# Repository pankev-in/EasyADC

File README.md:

#EasyADC

##Introduction

This is a brief documentation about EasyADC. But what's is it? 

Just like its name, it is a easy-to-use ADC converter using AVR(basically just plug and play). It is a small device with a ATmega8 on board and can do several things at the same time. If you want to see it in action, please visit my project Website ([k-pan.com](k-pan.com))

This device provides various functions:

1. Read/Test Analog Sensors with- or without a external Terminal. You can either read the value with the on-board LCD 16x2 Display or grab the information from the USB serial port.
2. It comes with an onboard PWM generator too. You can use it as a signal source.

####Specifications:
Connections:
	- 5 x 3.3V 
	- 5 x 5V 
	- 5 x GND 
	- 5 x Analog input port (for ADC)
	- 1 x 5k potentiometer (to adjust PWM signal, but you can also read on lcd or usb)
 	- 1 x PWM output

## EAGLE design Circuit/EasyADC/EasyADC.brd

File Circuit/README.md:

# EasyADC - Circuit

### This board is created with Eagle(V7.3).
### Just import it and should be good to go

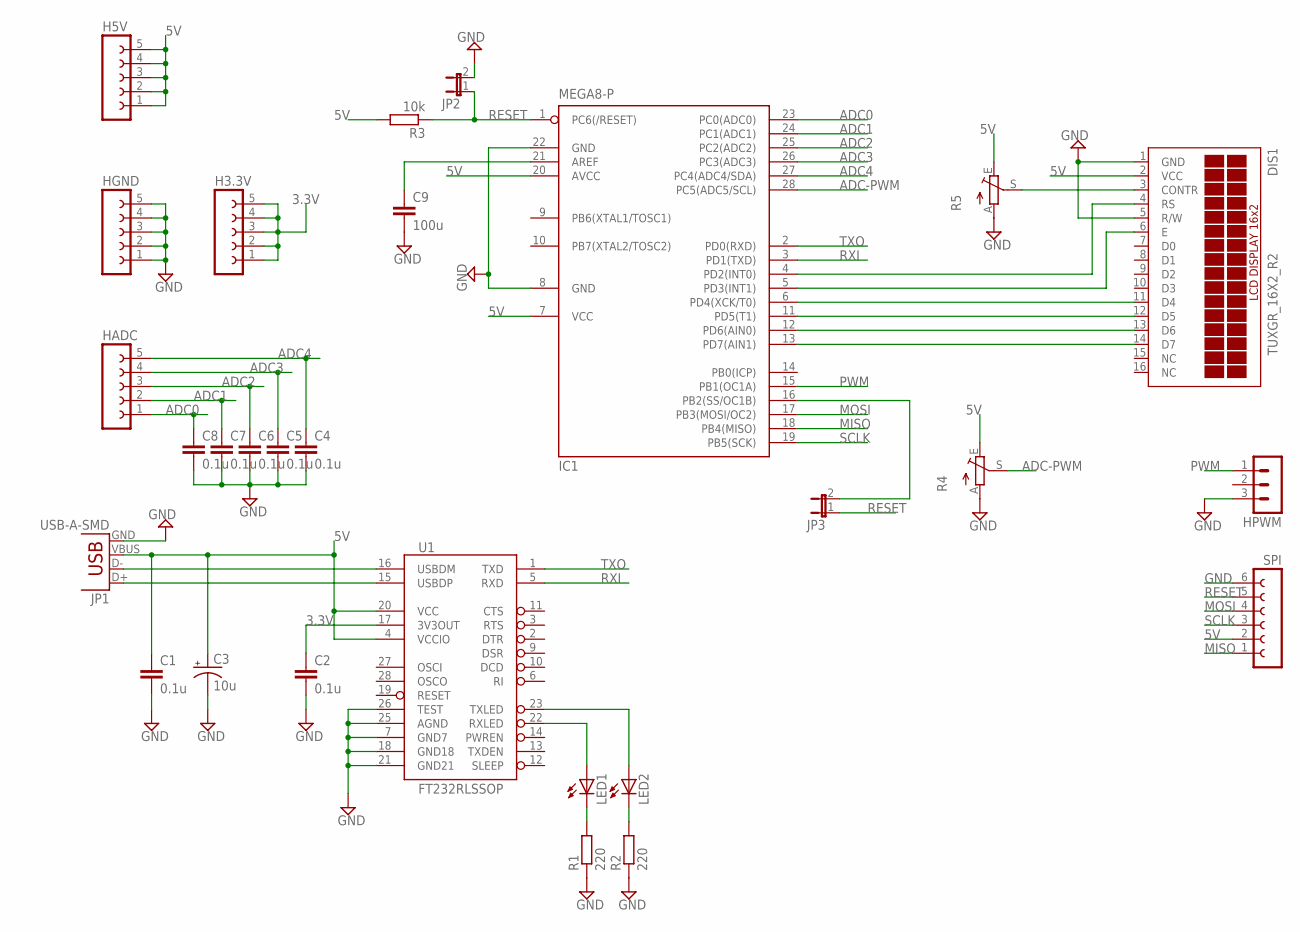
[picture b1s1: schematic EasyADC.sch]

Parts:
C1, C2, C4, C5, C6, C7, C8: 0.1u; C050-045X075
C3: 10u; CPOL-RADIAL-10UF-25V
C9: 100u; C050-075X075
DIS1: TUXGR_16X2_R2
H3.3V, H5V: FE05-1
HADC: FE05-1
HGND: FE05-1
HPWM: MA03-1
IC1: MEGA8-P; DIL28-3
JP1: USB-A-SMD; USB-A-S-NOSILK-FEMALE
JP2, JP3: JUMPER-2PTH; 1X02
LED1, LED2: LED3MM
R1, R2: 220; 0207/10
R3: 10k; 0207/10
R4, R5: TRIM_EU-CA6H; CA6H
SPI: FE06-1; FE06
U1: FT232RLSSOP; SSOP28DB

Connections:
3.3V: C2.1, H3.3V.1, H3.3V.2, H3.3V.3, H3.3V.4, H3.3V.5, U1.17 (3V3OUT)
5V: C1.1, C3.1 (+), DIS1.2 (VCC), H5V.1, H5V.2, H5V.3, H5V.4, H5V.5, IC1.7 (VCC), IC1.20 (AVCC), JP1.VBUS, R3.2, R4.E, R5.E, SPI.2, U1.4 (VCCIO), U1.20 (VCC)
ADC0: C8.1, HADC.1, IC1.23 (PC0(ADC0))
ADC1: C7.1, HADC.2, IC1.24 (PC1(ADC1))
ADC2: C6.1, HADC.3, IC1.25 (PC2(ADC2))
ADC3: C5.1, HADC.4, IC1.26 (PC3(ADC3))
ADC4: C4.1, HADC.5, IC1.27 (PC4(ADC4/SDA))
ADC-PWM: IC1.28 (PC5(ADC5/SCL)), R4.S
GND: C1.2, C2.2, C3.2 (-), C4.2, C5.2, C6.2, C7.2, C8.2, C9.2, DIS1.1 (GND), DIS1.5 (R/W), HGND.1, HGND.2, HGND.3, HGND.4, HGND.5, HPWM.3, IC1.8 (GND), IC1.22 (GND), JP1.GND, JP2.2, R1.1, R2.1, R4.A, R5.A, SPI.6, U1.7 (GND7), U1.18 (GND18), U1.21 (GND21), U1.25 (AGND), U1.26 (TEST)
MISO: IC1.18 (PB4(MISO)), SPI.1
MOSI: IC1.17 (PB3(MOSI/OC2)), SPI.4
unnamed: LED1.A, U1.22 (RXLED)
unnamed: JP1.D-, U1.16 (USBDM)
unnamed: JP1.D+, U1.15 (USBDP)
unnamed: LED2.A, U1.23 (TXLED)
unnamed: LED1.K (C), R1.2
unnamed: LED2.K (C), R2.2
unnamed: DIS1.14 (D7), IC1.13 (PD7(AIN1))
unnamed: DIS1.13 (D6), IC1.12 (PD6(AIN0))
unnamed: DIS1.12 (D5), IC1.11 (PD5(T1))
unnamed: DIS1.11 (D4), IC1.6 (PD4(XCK/T0))
unnamed: DIS1.4 (RS), IC1.4 (PD2(INT0))
unnamed: DIS1.6 (E), IC1.5 (PD3(INT1))
unnamed: DIS1.3 (CONTR), R5.S
unnamed: C9.1, IC1.21 (AREF)
unnamed: IC1.16 (PB2(SS/OC1B)), JP3.2
PWM: HPWM.1, IC1.15 (PB1(OC1A))
RESET: IC1.1 (PC6(/RESET)), JP2.1, JP3.1, R3.1, SPI.5
RXI: IC1.3 (PD1(TXD)), U1.5 (RXD)
SCLK: IC1.19 (PB5(SCK)), SPI.3
TXO: IC1.2 (PD0(RXD)), U1.1 (TXD)

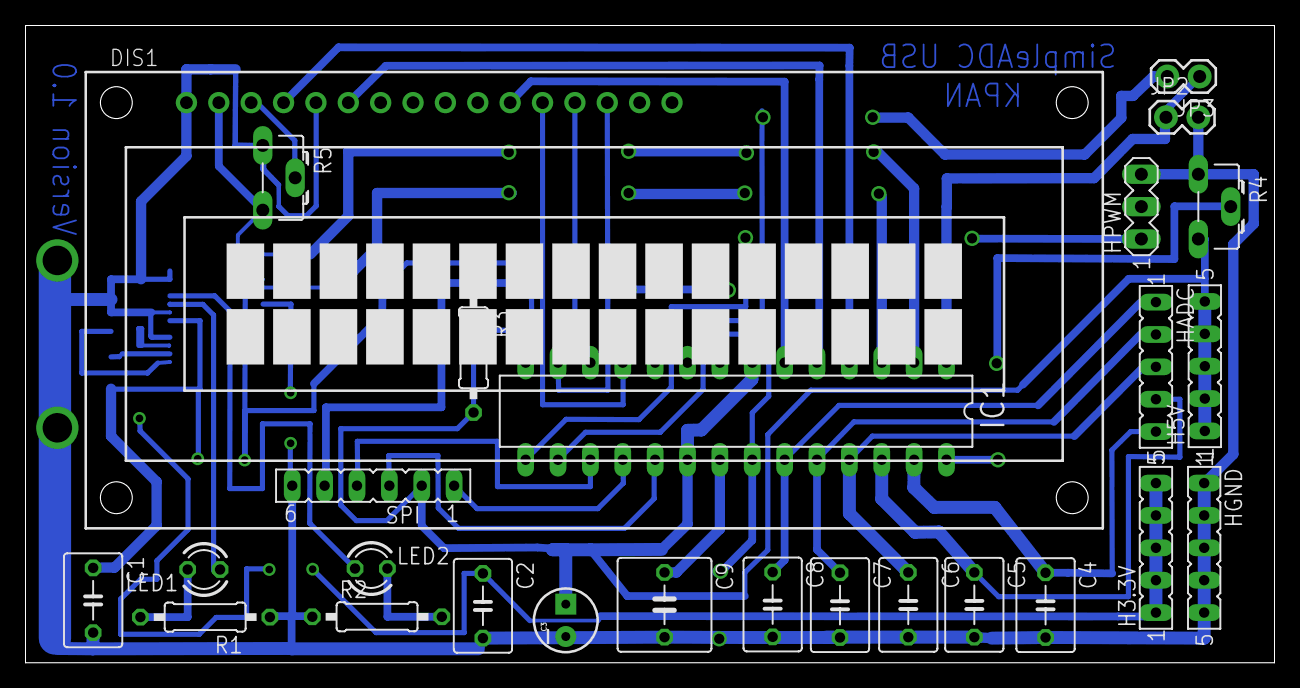
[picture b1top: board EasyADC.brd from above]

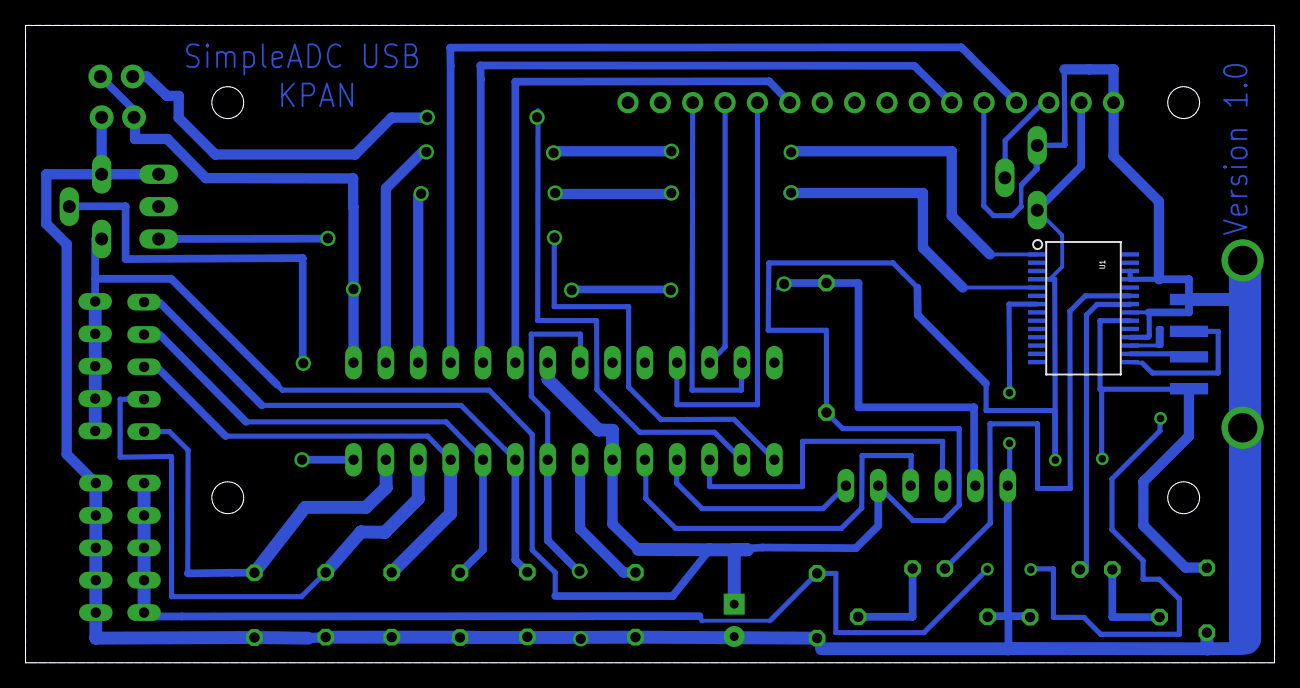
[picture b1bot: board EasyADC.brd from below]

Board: 2 copper layers, 98.0 x 50.0 mm, 28 parts (2 on the bottom side), 31 nets.

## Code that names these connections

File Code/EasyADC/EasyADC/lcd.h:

#ifndef LCD_H
#define LCD_H

////////////////////////////////////////////////////////////////////////////////
// Hier die verwendete Taktfrequenz in Hz eintragen, wichtig!

#ifndef F_CPU
#define F_CPU 8000000
#endif

////////////////////////////////////////////////////////////////////////////////
// Pinbelegung für das LCD, an verwendete Pins anpassen
// Alle LCD Pins müssen an einem Port angeschlossen sein und die 4
// Datenleitungen müssen auf aufeinanderfolgenden Pins liegen

//  LCD DB4-DB7 <-->  PORTD Bit PD4-PD7
#define LCD_PORT      PORTD
#define LCD_DDR       DDRD
#define LCD_DB        PD4

//  LCD RS      <-->  PORTD Bit PD2     (RS: 1=Data, 0=Command)
#define LCD_RS        PD2

//  LCD EN      <-->  PORTD Bit PD3     (EN: 1-Impuls für Daten)
#define LCD_EN        PD3

////////////////////////////////////////////////////////////////////////////////
// LCD Ausführungszeiten (MS=Millisekunden, US=Mikrosekunden)

#define LCD_BOOTUP_MS           15
#define LCD_ENABLE_US           20
#define LCD_WRITEDATA_US        46
#define LCD_COMMAND_US          42

#define LCD_SOFT_RESET_MS1      5
#define LCD_SOFT_RESET_MS2      1
#define LCD_SOFT_RESET_MS3      1
#define LCD_SET_4BITMODE_MS     5

#define LCD_CLEAR_DISPLAY_MS    2
#define LCD_CURSOR_HOME_MS      2

////////////////////////////////////////////////////////////////////////////////
// Zeilendefinitionen des verwendeten LCD
// Die Einträge hier sollten für ein LCD mit einer Zeilenlänge von 16 Zeichen passen
// Bei anderen Zeilenlängen müssen diese Einträge angepasst werden

#define LCD_DDADR_LINE1         0x00
#define LCD_DDADR_LINE2         0x40
#define LCD_DDADR_LINE3         0x10
#define LCD_DDADR_LINE4         0x50

////////////////////////////////////////////////////////////////////////////////
// Initialisierung: muss ganz am Anfang des Programms aufgerufen werden.
void lcd_init( void );

////////////////////////////////////////////////////////////////////////////////
// LCD löschen
void lcd_clear( void );

////////////////////////////////////////////////////////////////////////////////
// Cursor in die 1. Zeile, 0-te Spalte
void lcd_home( void );

////////////////////////////////////////////////////////////////////////////////
// Cursor an eine beliebige Position
void lcd_setcursor( uint8_t spalte, uint8_t zeile );

////////////////////////////////////////////////////////////////////////////////
// Ausgabe eines einzelnen Zeichens an der aktuellen Cursorposition
void lcd_data( uint8_t data );

////////////////////////////////////////////////////////////////////////////////
// Ausgabe eines Strings an der aktuellen Cursorposition
void lcd_string( const char *data );

////////////////////////////////////////////////////////////////////////////////
// Definition eines benutzerdefinierten Sonderzeichens.
// data muss auf ein Array[8] mit den Zeilencodes des zu definierenden Zeichens
// zeigen
void lcd_generatechar( uint8_t code, const uint8_t *data );

////////////////////////////////////////////////////////////////////////////////
// Ausgabe eines Kommandos an das LCD.
void lcd_command( uint8_t data );


////////////////////////////////////////////////////////////////////////////////
// LCD Befehle und Argumente.
// Zur Verwendung in lcd_command

// Clear Display -------------- 0b00000001
#define LCD_CLEAR_DISPLAY       0x01

// Cursor Home ---------------- 0b0000001x
#define LCD_CURSOR_HOME         0x02

// Set Entry Mode ------------- 0b000001xx
#define LCD_SET_ENTRY           0x04

#define LCD_ENTRY_DECREASE      0x00
#define LCD_ENTRY_INCREASE      0x02
#define LCD_ENTRY_NOSHIFT       0x00
#define LCD_ENTRY_SHIFT         0x01

// Set Display ---------------- 0b00001xxx
#define LCD_SET_DISPLAY         0x08

#define LCD_DISPLAY_OFF         0x00
#define LCD_DISPLAY_ON          0x04
#define LCD_CURSOR_OFF          0x00
#define LCD_CURSOR_ON           0x02
#define LCD_BLINKING_OFF        0x00
#define LCD_BLINKING_ON         0x01

// Set Shift ------------------ 0b0001xxxx
#define LCD_SET_SHIFT           0x10

#define LCD_CURSOR_MOVE         0x00
#define LCD_DISPLAY_SHIFT       0x08
#define LCD_SHIFT_LEFT          0x00
#define LCD_SHIFT_RIGHT         0x04

// Set Function --------------- 0b001xxxxx
#define LCD_SET_FUNCTION        0x20

#define LCD_FUNCTION_4BIT       0x00
#define LCD_FUNCTION_8BIT       0x10
#define LCD_FUNCTION_1LINE      0x00
#define LCD_FUNCTION_2LINE      0x08
#define LCD_FUNCTION_5X7        0x00
#define LCD_FUNCTION_5X10       0x04

#define LCD_SOFT_RESET          0x30

// Set CG RAM Address --------- 0b01xxxxxx  (Character Generator RAM)
#define LCD_SET_CGADR           0x40

#define LCD_GC_CHAR0            0
#define LCD_GC_CHAR1            1
#define LCD_GC_CHAR2            2
#define LCD_GC_CHAR3            3
#define LCD_GC_CHAR4            4
#define LCD_GC_CHAR5            5
#define LCD_GC_CHAR6            6
#define LCD_GC_CHAR7            7

// Set DD RAM Address --------- 0b1xxxxxxx  (Display Data RAM)
#define LCD_SET_DDADR           0x80

#endif

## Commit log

2015-07-09 init
    init
2015-07-14 Add Source Code
2015-07-14 Final Cleanup
2015-07-14 notes and circuit added
2015-07-15 Changed Discription
2015-07-15 image

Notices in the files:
parts and their libraries:
SparkFun-Capacitors: Licensing: Creative Commons ShareAlike 4.0 International - https://creativecommons.org/licenses/by-sa/4.0
